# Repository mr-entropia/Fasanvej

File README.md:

# Fasanvej
A hand-held Linux computer, inspired by Brian Benchoff's similar project

## Features
- Allwinner F1C200s SoC, an ARM926EJ-S running at 500 MHz
- 64 MB DDR DRAM, embedded in the SoC
- 3.2" TFT LCD, 320x240 resolution
- QWERTY keyboard (implemented using a SAMD21 MCU, connects via USB)
- Game mode switch which alters key mapping
- USB hub with one external USB A connector
- Internal USB A type connector for a miniature WiFi adapter
- Mono speaker
- microSD slot
- SPI NOR FLASH
- Powered by 2P1S 18650 li-ion battery
- Built-in charger using a USB C type connector
- High efficiency DC-DC converters to power everything

## Task list
- [x] Finalize schematics
- [x] Place components on PCB
- [ ] Route PCB
- [x] Design a 3D-printable enclosure
- [ ] Source parts
- [ ] Build prototype
- [ ] Make software work
- [ ] Play DOOM

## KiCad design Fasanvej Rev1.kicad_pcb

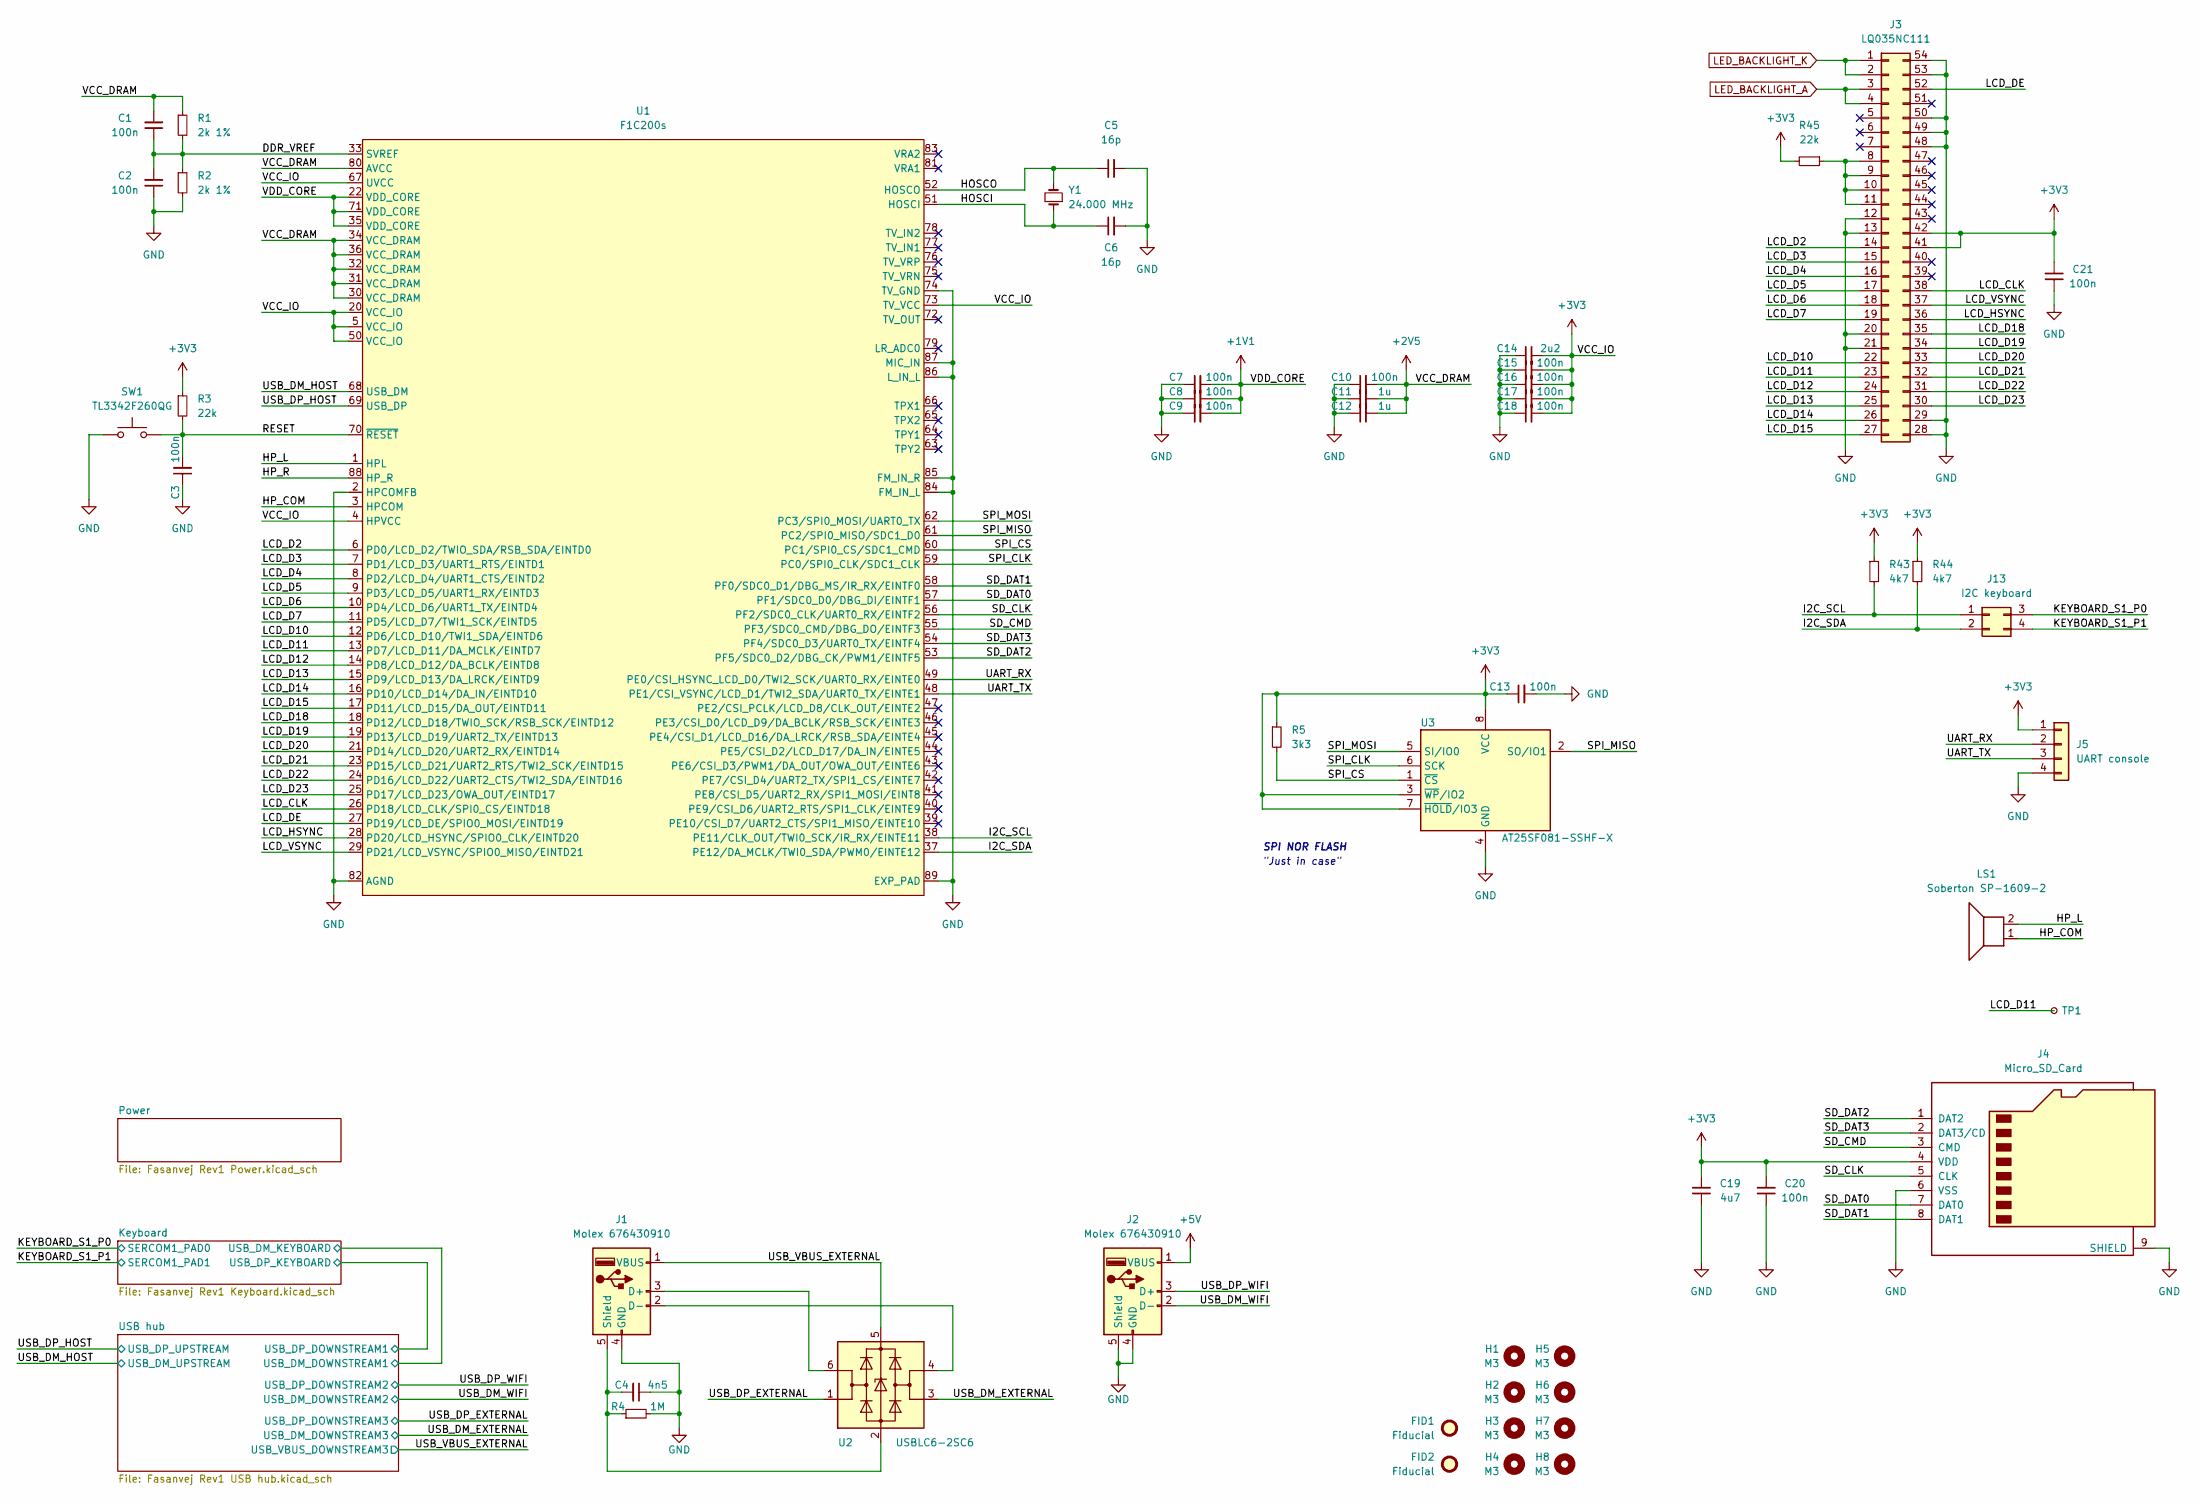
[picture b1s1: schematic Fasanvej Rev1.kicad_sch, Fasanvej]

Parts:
C1, C2, C3, C7, C8, C9, C10, C13, C15, C16, C17, C18, C20, C21: 100n; C_0603_1608Metric_Pad1.08x0.95mm_HandSolder
C4: 4n5; C_0603_1608Metric_Pad1.08x0.95mm_HandSolder
C5, C6: 16p; C_0603_1608Metric_Pad1.08x0.95mm_HandSolder
C11, C12: 1u; C_0805_2012Metric_Pad1.18x1.45mm_HandSolder
C14: 2u2; C_0805_2012Metric_Pad1.18x1.45mm_HandSolder
C19: 4u7; C_0805_2012Metric_Pad1.18x1.45mm_HandSolder
FID1, FID2: Fiducial; Fiducial_1.5mm_Mask3mm
H1, H2, H3, H4, H5, H6, H7, H8: M3; MountingHole_3.2mm_M3
J1, J2: Molex 676430910; USB_A_Molex_67643_Horizontal
J3: LQ035NC111; FFC2B22-54-T
J4: Micro_SD_Card; microSD_HC_Hirose_DM3D-SF
J5: UART console; PinHeader_1x04_P2.54mm_Vertical
J13: I2C keyboard; PinHeader_2x02_P2.54mm_Vertical
LS1: Soberton SP-1609-2; PinHeader_1x02_P2.54mm_Vertical
R1, R2: 2k 1%; R_0603_1608Metric_Pad0.98x0.95mm_HandSolder
R3, R45: 22k; R_0603_1608Metric_Pad0.98x0.95mm_HandSolder
R4: 1M; R_0603_1608Metric_Pad0.98x0.95mm_HandSolder
R5: 3k3; R_0603_1608Metric_Pad0.98x0.95mm_HandSolder
R43, R44: 4k7; R_0603_1608Metric_Pad0.98x0.95mm_HandSolder
SW1: TL3342F260QG; SW_SPST_TL3342
TP1: TestPoint_Small; TestPoint_Pad_D2.5mm
U1: F1C200s; QFN-88_EP_10x10_Pitch0.4mm
U2: USBLC6-2SC6; SOT-23-6
U3: AT25SF081-SSHF-X; SOIC-8_3.9x4.9mm_P1.27mm
Y1: 24.000 MHz; Crystal_SMD_HC49-SD_HandSoldering

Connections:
+1V1: C7.2, C8.2, C9.2, U1.22 (VDD_CORE), U1.35 (VDD_CORE), U1.71 (VDD_CORE); also elsewhere on the board
+2V5: C1.2, C10.2, C11.2, C12.2, R1.1, U1.30 (VCC_DRAM), U1.31 (VCC_DRAM), U1.32 (VCC_DRAM), U1.34 (VCC_DRAM), U1.36 (VCC_DRAM), U1.80 (AVCC); also elsewhere on the board
+3V3: C13.1, C14.2, C15.2, C16.2, C17.2, C18.2, C19.2, C20.2, C21.2, J3.41, J3.42, J4.4 (VDD), J5.1, R3.1, R5.1, R43.1, R44.1, R45.2, U1.4 (HPVCC), U1.5 (VCC_IO), U1.20 (VCC_IO), U1.50 (VCC_IO), U1.67 (UVCC), U1.73 (TV_VCC), U3.3 (~WP/IO2), U3.7 (~HOLD/IO3), U3.8 (VCC); also elsewhere on the board
+5V: J2.1 (VBUS); also elsewhere on the board
/DDR_VREF: C1.1, C2.2, R1.2, R2.1, U1.33 (SVREF)
/HOSCI: C6.1, U1.51 (HOSCI), Y1.1
/HOSCO: C5.1, U1.52 (HOSCO), Y1.2
/HP_COM: LS1.1, U1.3 (HPCOM)
/HP_L: LS1.2, U1.1 (HPL)
/HP_R: U1.88 (HP_R)
/I2C_SCL: J13.1, R43.2, U1.38 (PE11/CLK_OUT/TWI0_SCK/IR_RX/EINTE11)
/I2C_SDA: J13.2, R44.2, U1.37 (PE12/DA_MCLK/TWI0_SDA/PWM0/EINTE12)
/KEYBOARD_S1_P0: J13.3; also elsewhere on the board
/KEYBOARD_S1_P1: J13.4; also elsewhere on the board
/LCD_CLK: J3.38, U1.26 (PD18/LCD_CLK/SPI0_CS/EINTD18)
/LCD_D2: J3.14, U1.6 (PD0/LCD_D2/TWIO_SDA/RSB_SDA/EINTD0)
/LCD_D3: J3.15, U1.7 (PD1/LCD_D3/UART1_RTS/EINTD1)
/LCD_D4: J3.16, U1.8 (PD2/LCD_D4/UART1_CTS/EINTD2)
/LCD_D5: J3.17, U1.9 (PD3/LCD_D5/UART1_RX/EINTD3)
/LCD_D6: J3.18, U1.10 (PD4/LCD_D6/UART1_TX/EINTD4)
/LCD_D7: J3.19, U1.11 (PD5/LCD_D7/TWI1_SCK/EINTD5)
/LCD_D10: J3.22, U1.12 (PD6/LCD_D10/TWI1_SDA/EINTD6)
/LCD_D11: J3.23, TP1.1, U1.13 (PD7/LCD_D11/DA_MCLK/EINTD7)
/LCD_D12: J3.24, U1.14 (PD8/LCD_D12/DA_BCLK/EINTD8)
/LCD_D13: J3.25, U1.15 (PD9/LCD_D13/DA_LRCK/EINTD9)
/LCD_D14: J3.26, U1.16 (PD10/LCD_D14/DA_IN/EINTD10)
/LCD_D15: J3.27, U1.17 (PD11/LCD_D15/DA_OUT/EINTD11)
/LCD_D18: J3.35, U1.18 (PD12/LCD_D18/TWIO_SCK/RSB_SCK/EINTD12)
/LCD_D19: J3.34, U1.19 (PD13/LCD_D19/UART2_TX/EINTD13)
/LCD_D20: J3.33, U1.21 (PD14/LCD_D20/UART2_RX/EINTD14)
/LCD_D21: J3.32, U1.23 (PD15/LCD_D21/UART2_RTS/TWI2_SCK/EINTD15)
/LCD_D22: J3.31, U1.24 (PD16/LCD_D22/UART2_CTS/TWI2_SDA/EINTD16)
/LCD_D23: J3.30, U1.25 (PD17/LCD_D23/OWA_OUT/EINTD17)
/LCD_DE: J3.52, U1.27 (PD19/LCD_DE/SPIO0_MOSI/EINTD19)
/LCD_HSYNC: J3.36, U1.28 (PD20/LCD_HSYNC/SPIO0_CLK/EINTD20)
/LCD_VSYNC: J3.37, U1.29 (PD21/LCD_VSYNC/SPIO0_MISO/EINTD21)
/RESET: C3.2, R3.2, SW1.2, U1.70 (~RESET)
/SD_CLK: J4.5 (CLK), U1.56 (PF2/SDC0_CLK/UART0_RX/EINTF2)
/SD_CMD: J4.3 (CMD), U1.55 (PF3/SDC0_CMD/DBG_DO/EINTF3)
/SD_DAT0: J4.7 (DAT0), U1.57 (PF1/SDC0_D0/DBG_DI/EINTF1)
/SD_DAT1: J4.8 (DAT1), U1.58 (PF0/SDC0_D1/DBG_MS/IR_RX/EINTF0)
/SD_DAT2: J4.1 (DAT2), U1.53 (PF5/SDC0_D2/DBG_CK/PWM1/EINTF5)
/SD_DAT3: J4.2 (DAT3/CD), U1.54 (PF4/SDC0_D3/UART0_TX/EINTF4)
/SPI_CLK: U1.59 (PC0/SPI0_CLK/SDC1_CLK), U3.6 (SCK)
/SPI_CS: R5.2, U1.60 (PC1/SPI0_CS/SDC1_CMD), U3.1 (~CS)
/SPI_MISO: U1.61 (PC2/SPI0_MISO/SDC1_D0), U3.2 (SO/IO1)
/SPI_MOSI: U1.62 (PC3/SPI0_MOSI/UART0_TX), U3.5 (SI/IO0)
/UART_RX: J5.2, U1.49 (PE0/CSI_HSYNC_LCD_D0/TWI2_SCK/UART0_RX/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)
/UART_TX: J5.3, U1.48 (PE1/CSI_VSYNC/LCD_D1/TWI2_SDA/UART0_TX/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)
/USB_DM_EXTERNAL: U2.3 (I/O2); also elsewhere on the board
/USB_DM_HOST: U1.68 (USB_DM); also elsewhere on the board
/USB_DM_WIFI: J2.2 (D-); also elsewhere on the board
/USB_DP_EXTERNAL: U2.1 (I/O1); also elsewhere on the board
/USB_DP_HOST: U1.69 (USB_DP); also elsewhere on the board
/USB_DP_WIFI: J2.3 (D+); also elsewhere on the board
/USB_VBUS_EXTERNAL: J1.1 (VBUS), U2.5 (VBUS); also elsewhere on the board
GND: C2.1, C3.1, C4.1, C5.2, C6.2, C7.1, C8.1, C9.1, C10.1, C11.1, C12.1, C13.2, C14.1, C15.1, C16.1, C17.1, C18.1, C19.1, C20.1, C21.1, J1.4 (GND), J2.4 (GND), J2.5 (Shield), J3.12, J3.13, J3.20, J3.21, J3.28, J3.29, J3.48, J3.49, J3.50, J3.53, J3.54, J4.6 (VSS), J4.9 (SHIELD), J5.4, R2.2, R4.2, SW1.1, U1.2 (HPCOMFB), U1.74 (TV_GND), U1.82 (AGND), U1.84 (FM_IN_L), U1.85 (FM_IN_R), U1.86 (L_IN_L), U1.87 (MIC_IN), U1.89 (EXP_PAD), U3.4 (GND); also elsewhere on the board
LED_BACKLIGHT_A: J3.3, J3.4; also elsewhere on the board
LED_BACKLIGHT_K: J3.1, J3.2; also elsewhere on the board
unnamed: C4.2, J1.5 (Shield), R4.1, U2.2 (GND)
unnamed: J1.2 (D-), U2.4 (I/O2)
unnamed: J1.3 (D+), U2.6 (I/O1)
unnamed: J3.8, J3.9, J3.10, J3.11, R45.1

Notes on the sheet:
SPI NOR FLASH
"Just in case"

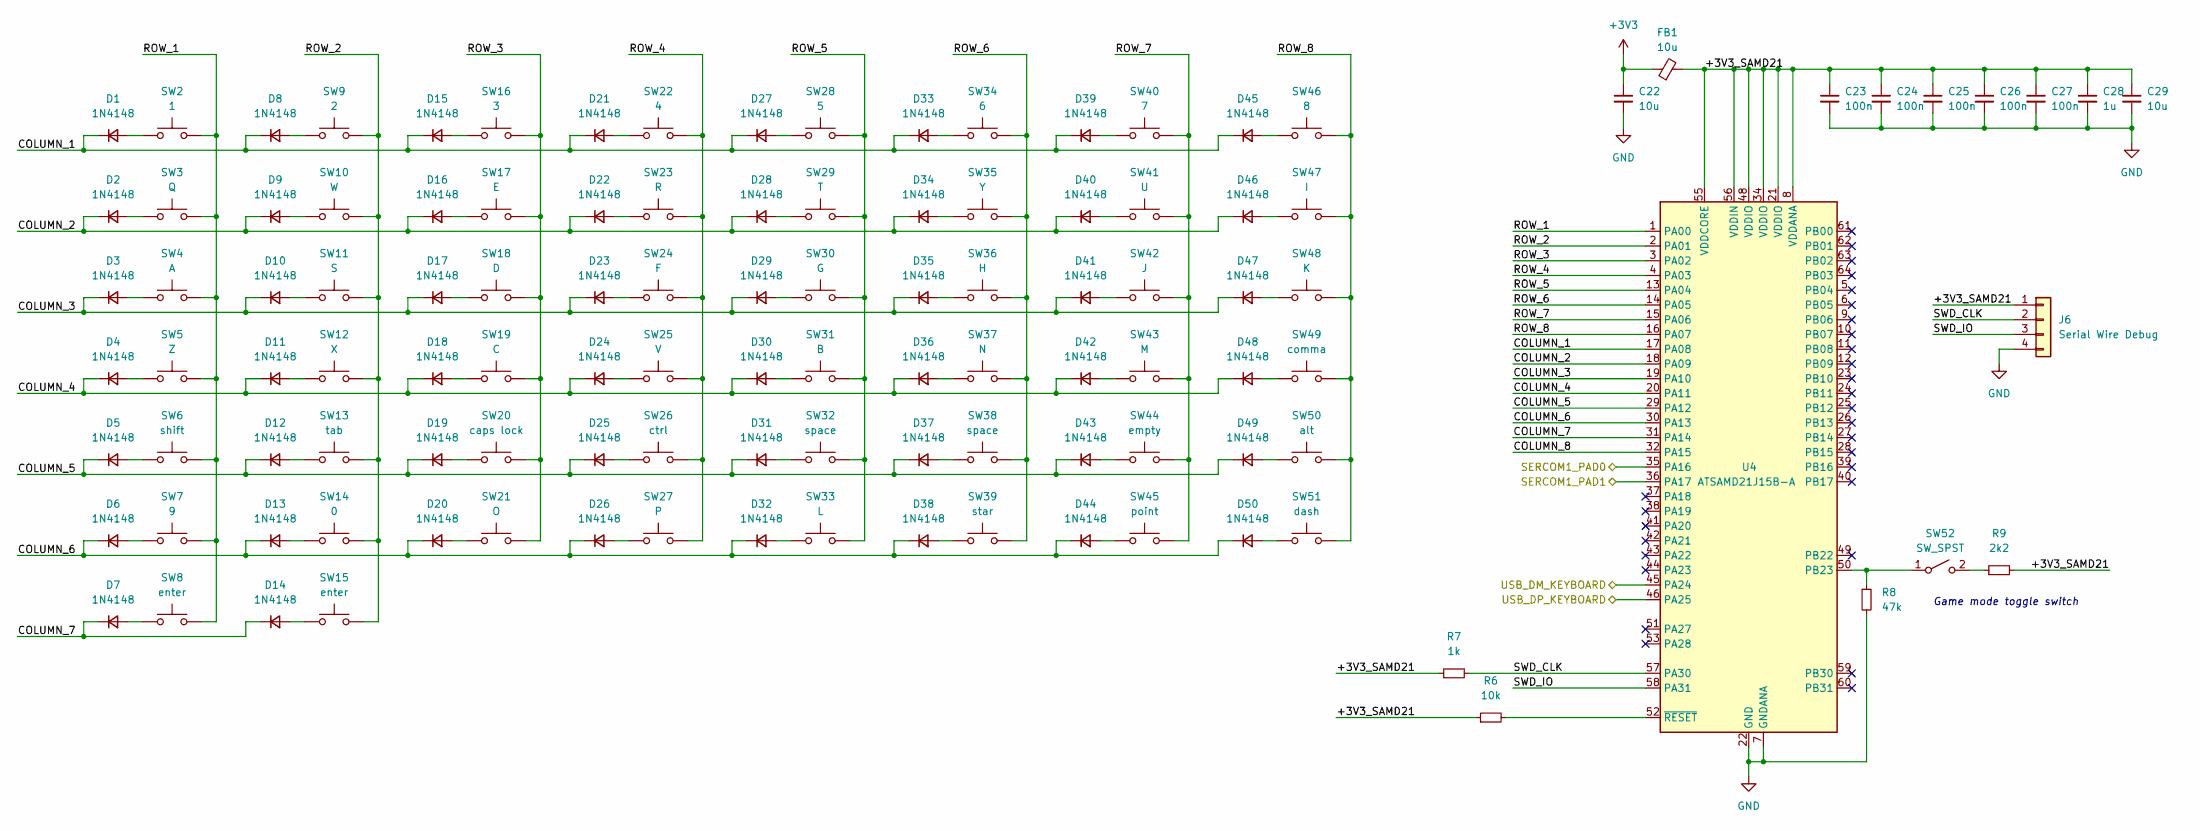
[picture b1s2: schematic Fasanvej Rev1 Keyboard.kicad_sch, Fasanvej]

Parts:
C22, C29: 10u; C_1206_3216Metric_Pad1.33x1.80mm_HandSolder
C23, C24, C25, C26, C27: 100n; C_0603_1608Metric_Pad1.08x0.95mm_HandSolder
C28: 1u; C_0603_1608Metric_Pad1.08x0.95mm_HandSolder
D1, D2, D3, D4, D5, D6, D7, D8, D9, D10, D11, D12, D13, D14, D15, D16, D17, D18, D19, D20, D21, D22, D23, D24, D25, D26, D27, D28, D29, D30, D31, D32, D33, D34, D35, D36, D37, D38, D39, D40, D41, D42, D43, D44, D45, D46, D47, D48, D49, D50: 1N4148; D_SOD-323_HandSoldering
FB1: 10u; L_1206_3216Metric_Pad1.22x1.90mm_HandSolder
J6: Serial Wire Debug; PinHeader_1x04_P2.54mm_Vertical
R6: 10k; R_0603_1608Metric_Pad0.98x0.95mm_HandSolder
R7: 1k; R_0603_1608Metric_Pad0.98x0.95mm_HandSolder
R8: 47k; R_0603_1608Metric_Pad0.98x0.95mm_HandSolder
R9: 2k2; R_0603_1608Metric_Pad0.98x0.95mm_HandSolder
SW2: 1; SW_SPST_TL3342
SW3: Q; SW_SPST_TL3342
SW4: A; SW_SPST_TL3342
SW5: Z; SW_SPST_TL3342
SW6: shift; SW_SPST_TL3342
SW7: 9; SW_SPST_TL3342
SW8, SW15: enter; SW_SPST_TL3342
SW9: 2; SW_SPST_TL3342
SW10: W; SW_SPST_TL3342
SW11: S; SW_SPST_TL3342
SW12: X; SW_SPST_TL3342
SW13: tab; SW_SPST_TL3342
SW14: 0; SW_SPST_TL3342
SW16: 3; SW_SPST_TL3342
SW17: E; SW_SPST_TL3342
SW18: D; SW_SPST_TL3342
SW19: C; SW_SPST_TL3342
SW20: caps lock; SW_SPST_TL3342
SW21: O; SW_SPST_TL3342
SW22: 4; SW_SPST_TL3342
SW23: R; SW_SPST_TL3342
SW24: F; SW_SPST_TL3342
SW25: V; SW_SPST_TL3342
SW26: ctrl; SW_SPST_TL3342
SW27: P; SW_SPST_TL3342
SW28: 5; SW_SPST_TL3342
SW29: T; SW_SPST_TL3342
SW30: G; SW_SPST_TL3342
SW31: B; SW_SPST_TL3342
SW32, SW38: space; SW_SPST_TL3342
SW33: L; SW_SPST_TL3342
SW34: 6; SW_SPST_TL3342
SW35: Y; SW_SPST_TL3342
SW36: H; SW_SPST_TL3342
SW37: N; SW_SPST_TL3342
SW39: star; SW_SPST_TL3342
SW40: 7; SW_SPST_TL3342
SW41: U; SW_SPST_TL3342
SW42: J; SW_SPST_TL3342
SW43: M; SW_SPST_TL3342
SW44: empty; SW_SPST_TL3342
SW45: point; SW_SPST_TL3342
SW46: 8; SW_SPST_TL3342
SW47: I; SW_SPST_TL3342
SW48: K; SW_SPST_TL3342
SW49: comma; SW_SPST_TL3342
SW50: alt; SW_SPST_TL3342
SW51: dash; SW_SPST_TL3342
SW52: SW_SPST; SW_CuK_JS202011AQN_DPDT_Angled
U4: ATSAMD21J15B-A; TQFP-64_10x10mm_P0.5mm

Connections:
+3V3: C22.1, FB1.1; also elsewhere on the board
/KEYBOARD_S1_P0: U4.35 (PA16); also elsewhere on the board
/KEYBOARD_S1_P1: U4.36 (PA17); also elsewhere on the board
/Keyboard/+3V3_SAMD21: C23.1, C24.1, C25.1, C26.1, C27.1, C28.1, C29.1, FB1.2, J6.1, R6.1, R7.1, R9.2, U4.8 (VDDANA), U4.21 (VDDIO), U4.34 (VDDIO), U4.48 (VDDIO), U4.55 (VDDCORE), U4.56 (VDDIN)
/Keyboard/COLUMN_1: D1.1 (K), D8.1 (K), D15.1 (K), D21.1 (K), D27.1 (K), D33.1 (K), D39.1 (K), D45.1 (K), U4.17 (PA08)
/Keyboard/COLUMN_2: D2.1 (K), D9.1 (K), D16.1 (K), D22.1 (K), D28.1 (K), D34.1 (K), D40.1 (K), D46.1 (K), U4.18 (PA09)
/Keyboard/COLUMN_3: D3.1 (K), D10.1 (K), D17.1 (K), D23.1 (K), D29.1 (K), D35.1 (K), D41.1 (K), D47.1 (K), U4.19 (PA10)
/Keyboard/COLUMN_4: D4.1 (K), D11.1 (K), D18.1 (K), D24.1 (K), D30.1 (K), D36.1 (K), D42.1 (K), D48.1 (K), U4.20 (PA11)
/Keyboard/COLUMN_5: D5.1 (K), D12.1 (K), D19.1 (K), D25.1 (K), D31.1 (K), D37.1 (K), D43.1 (K), D49.1 (K), U4.29 (PA12)
/Keyboard/COLUMN_6: D6.1 (K), D13.1 (K), D20.1 (K), D26.1 (K), D32.1 (K), D38.1 (K), D44.1 (K), D50.1 (K), U4.30 (PA13)
/Keyboard/COLUMN_7: D7.1 (K), D14.1 (K), U4.31 (PA14)
/Keyboard/COLUMN_8: U4.32 (PA15)
/Keyboard/ROW_1: SW2.2, SW3.2, SW4.2, SW5.2, SW6.2, SW7.2, SW8.2, U4.1 (PA00)
/Keyboard/ROW_2: SW9.2, SW10.2, SW11.2, SW12.2, SW13.2, SW14.2, SW15.2, U4.2 (PA01)
/Keyboard/ROW_3: SW16.2, SW17.2, SW18.2, SW19.2, SW20.2, SW21.2, U4.3 (PA02)
/Keyboard/ROW_4: SW22.2, SW23.2, SW24.2, SW25.2, SW26.2, SW27.2, U4.4 (PA03)
/Keyboard/ROW_5: SW28.2, SW29.2, SW30.2, SW31.2, SW32.2, SW33.2, U4.13 (PA04)
/Keyboard/ROW_6: SW34.2, SW35.2, SW36.2, SW37.2, SW38.2, SW39.2, U4.14 (PA05)
/Keyboard/ROW_7: SW40.2, SW41.2, SW42.2, SW43.2, SW44.2, SW45.2, U4.15 (PA06)
/Keyboard/ROW_8: SW46.2, SW47.2, SW48.2, SW49.2, SW50.2, SW51.2, U4.16 (PA07)
/Keyboard/SWD_CLK: J6.2, R7.2, U4.57 (PA30)
/Keyboard/SWD_IO: J6.3, U4.58 (PA31)
/Keyboard/USB_DM_KEYBOARD: U4.45 (PA24); also elsewhere on the board
/Keyboard/USB_DP_KEYBOARD: U4.46 (PA25); also elsewhere on the board
GND: C22.2, C23.2, C24.2, C25.2, C26.2, C27.2, C28.2, C29.2, J6.4, R8.2, U4.7 (GNDANA), U4.22 (GND), U4.33 (GND), U4.47 (GND), U4.54 (GND); also elsewhere on the board
unnamed: D1.2 (A), SW2.1
unnamed: D2.2 (A), SW3.1
unnamed: D3.2 (A), SW4.1
unnamed: D4.2 (A), SW5.1
unnamed: D5.2 (A), SW6.1
unnamed: D6.2 (A), SW7.1
unnamed: D7.2 (A), SW8.1
unnamed: D8.2 (A), SW9.1
unnamed: D9.2 (A), SW10.1
unnamed: D10.2 (A), SW11.1
unnamed: D11.2 (A), SW12.1
unnamed: D12.2 (A), SW13.1
unnamed: D13.2 (A), SW14.1
unnamed: D14.2 (A), SW15.1
unnamed: D15.2 (A), SW16.1
unnamed: D16.2 (A), SW17.1
unnamed: D17.2 (A), SW18.1
unnamed: D18.2 (A), SW19.1
unnamed: D19.2 (A), SW20.1
unnamed: D20.2 (A), SW21.1
unnamed: D21.2 (A), SW22.1
unnamed: D22.2 (A), SW23.1
unnamed: D23.2 (A), SW24.1
unnamed: D24.2 (A), SW25.1
unnamed: D25.2 (A), SW26.1
unnamed: D26.2 (A), SW27.1
unnamed: D27.2 (A), SW28.1
unnamed: D28.2 (A), SW29.1
unnamed: D29.2 (A), SW30.1
unnamed: D30.2 (A), SW31.1
unnamed: D31.2 (A), SW32.1
unnamed: D32.2 (A), SW33.1
unnamed: D33.2 (A), SW34.1
unnamed: D34.2 (A), SW35.1
unnamed: D35.2 (A), SW36.1
unnamed: D36.2 (A), SW37.1
unnamed: D37.2 (A), SW38.1
unnamed: D38.2 (A), SW39.1
unnamed: D39.2 (A), SW40.1
unnamed: D40.2 (A), SW41.1
unnamed: D41.2 (A), SW42.1
unnamed: D42.2 (A), SW43.1
unnamed: D43.2 (A), SW44.1
unnamed: D44.2 (A), SW45.1
unnamed: D45.2 (A), SW46.1
unnamed: D46.2 (A), SW47.1
unnamed: D47.2 (A), SW48.1
unnamed: D48.2 (A), SW49.1
unnamed: D49.2 (A), SW50.1
unnamed: D50.2 (A), SW51.1
unnamed: R6.2, U4.52 (~RESET)
unnamed: R8.1, SW52.1 (A), U4.50 (PB23)
unnamed: R9.1, SW52.2 (B)

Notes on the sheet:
Game mode toggle switch

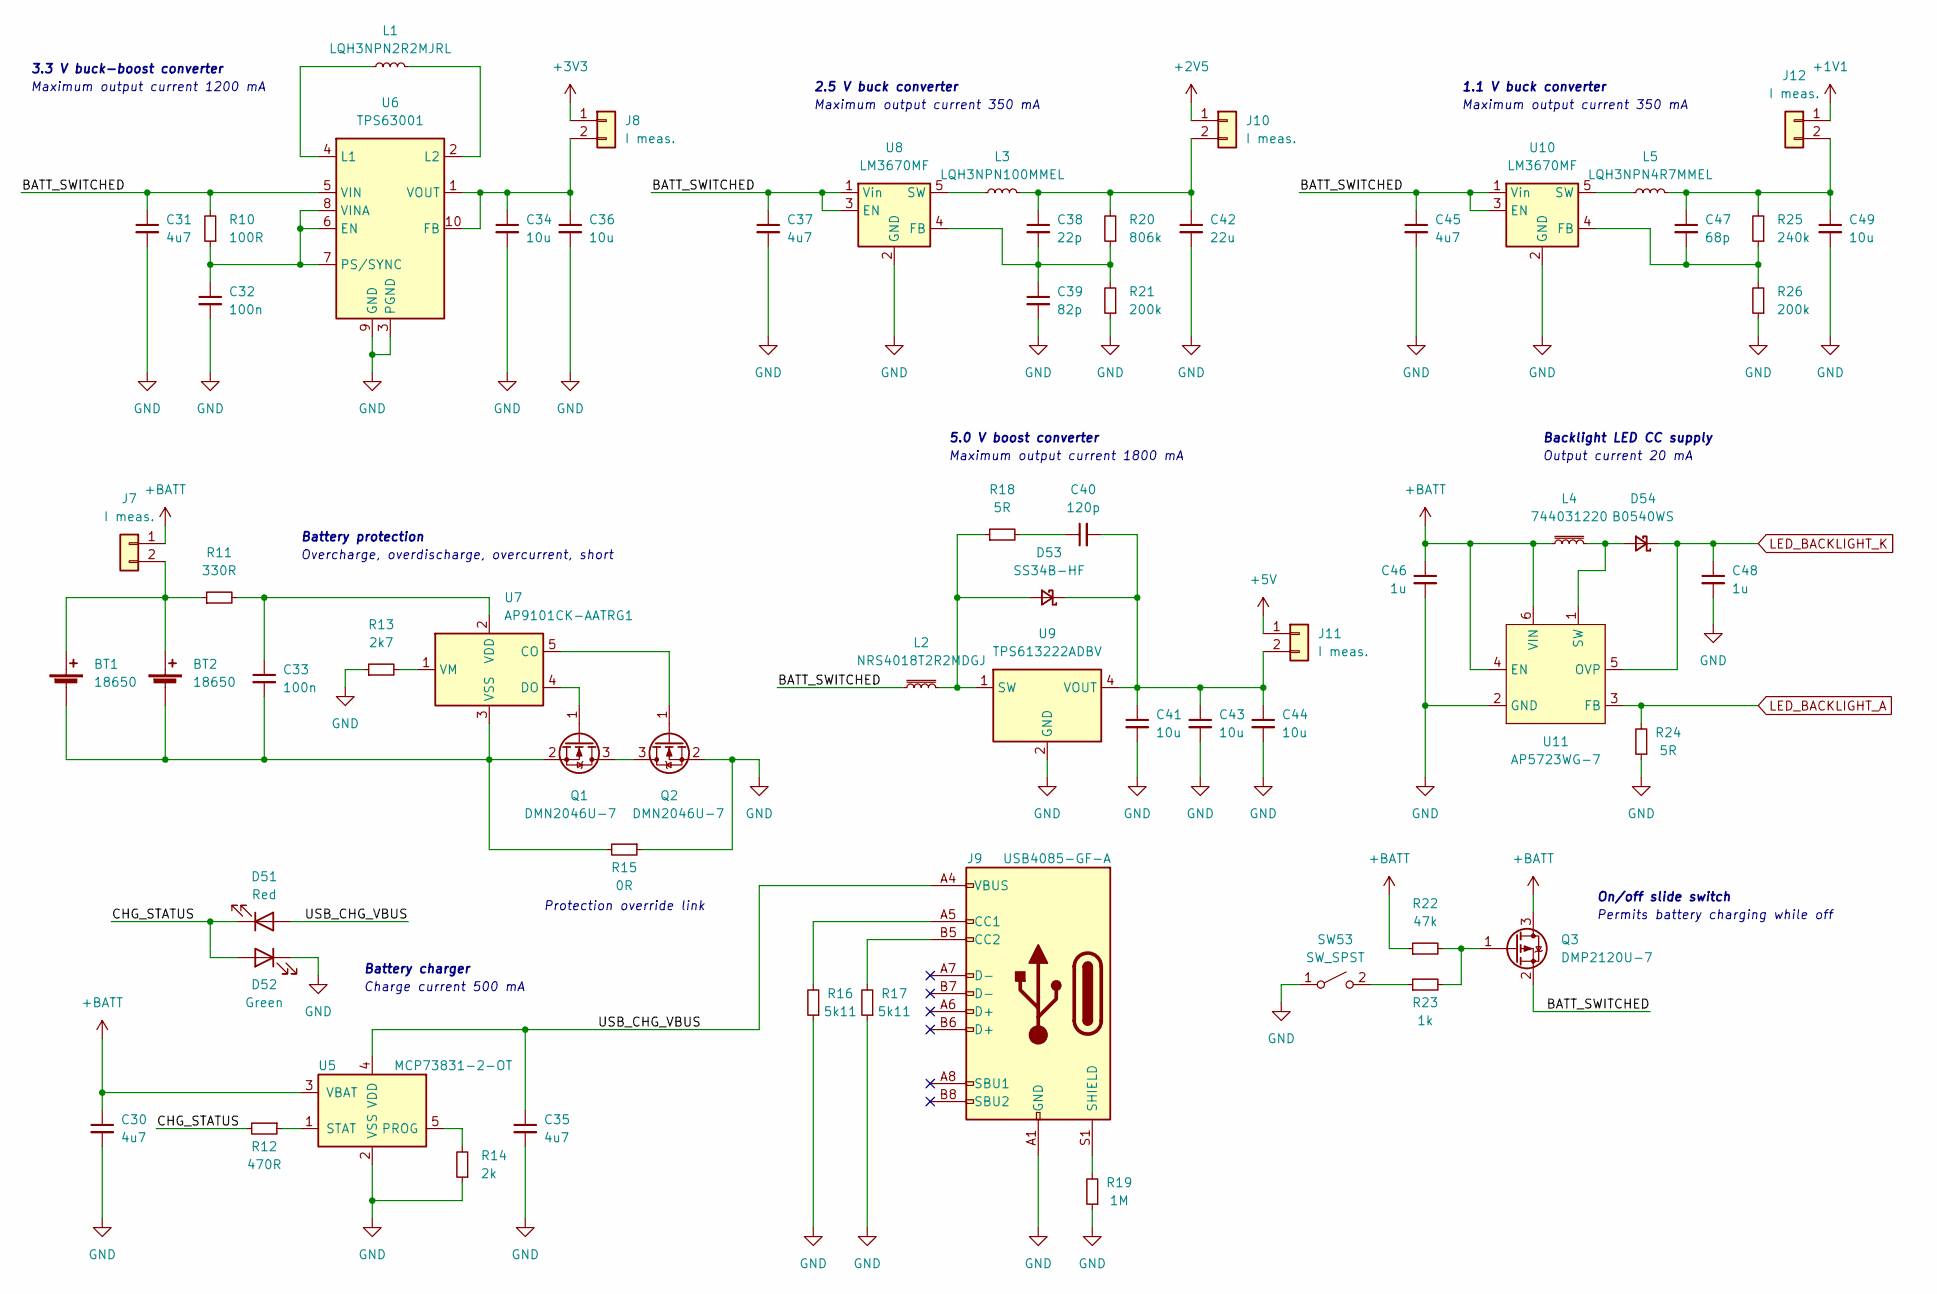
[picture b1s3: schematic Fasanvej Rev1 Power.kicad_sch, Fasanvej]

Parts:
BT1, BT2: 18650; BatteryHolder_Keystone_1042_1x18650
C30, C31, C35, C37, C45: 4u7; C_1206_3216Metric_Pad1.33x1.80mm_HandSolder
C32, C33: 100n; C_0603_1608Metric_Pad1.08x0.95mm_HandSolder
C34, C36, C41, C43, C44: 10u; C_1210_3225Metric_Pad1.33x2.70mm_HandSolder
C38: 22p; C_0603_1608Metric_Pad1.08x0.95mm_HandSolder
C39: 82p; C_0603_1608Metric_Pad1.08x0.95mm_HandSolder
C40: 120p; C_0603_1608Metric_Pad1.08x0.95mm_HandSolder
C42: 22u; C_1210_3225Metric_Pad1.33x2.70mm_HandSolder
C46, C48: 1u; C_0805_2012Metric_Pad1.18x1.45mm_HandSolder
C47: 68p; C_0603_1608Metric_Pad1.08x0.95mm_HandSolder
C49: 10u; C_1206_3216Metric_Pad1.33x1.80mm_HandSolder
D51: Red; LED_0805_2012Metric_Pad1.15x1.40mm_HandSolder
D52: Green; LED_0805_2012Metric_Pad1.15x1.40mm_HandSolder
D53: SS34B-HF; D_SMB_Handsoldering
D54: B0540WS; D_SOD-323_HandSoldering
J7, J8, J10, J11, J12: I meas.; PinHeader_1x02_P2.54mm_Vertical
J9: USB4085-GF-A; USB_C_Receptacle_GCT_USB4085
L1: LQH3NPN2R2MJRL; L_SMD_3030
L2: NRS4018T2R2MDGJ; L_Taiyo-Yuden_NR-40xx_HandSoldering
L3: LQH3NPN100MMEL; L_SMD_3030
L4: 744031220; L_Wuerth_WE-TPC-3816
L5: LQH3NPN4R7MMEL; L_SMD_3030
Q1, Q2: DMN2046U-7; SOT-23_Handsoldering
Q3: DMP2120U-7; SOT-23_Handsoldering
R10: 100R; R_0603_1608Metric_Pad0.98x0.95mm_HandSolder
R11: 330R; R_1206_3216Metric_Pad1.30x1.75mm_HandSolder
R12: 470R; R_0603_1608Metric_Pad0.98x0.95mm_HandSolder
R13: 2k7; R_1206_3216Metric_Pad1.30x1.75mm_HandSolder
R14: 2k; R_0603_1608Metric_Pad0.98x0.95mm_HandSolder
R15: 0R; R_1210_3225Metric_Pad1.30x2.65mm_HandSolder
R16, R17: 5k11; R_0603_1608Metric_Pad0.98x0.95mm_HandSolder
R18: 5R; R_0603_1608Metric_Pad0.98x0.95mm_HandSolder
R19: 1M; R_0603_1608Metric_Pad0.98x0.95mm_HandSolder
R20: 806k; R_0603_1608Metric_Pad0.98x0.95mm_HandSolder
R21, R26: 200k; R_0603_1608Metric_Pad0.98x0.95mm_HandSolder
R22: 47k; R_0603_1608Metric_Pad0.98x0.95mm_HandSolder
R23: 1k; R_0603_1608Metric_Pad0.98x0.95mm_HandSolder
R24: 5R; R_1210_3225Metric_Pad1.30x2.65mm_HandSolder
R25: 240k; R_0603_1608Metric_Pad0.98x0.95mm_HandSolder
SW53: SW_SPST; SW_CuK_JS202011AQN_DPDT_Angled
U5: MCP73831-2-OT; SOT-23-5
U6: TPS63001; Texas_DRC0010J_ThermalVias
U7: AP9101CK-AATRG1; SOT-23-5
U8, U10: LM3670MF; TSOT-23-5
U9: TPS613222ADBV; SOT-23-5
U11: AP5723WG-7; SOT-23-6_Handsoldering

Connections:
+1V1: J12.1; also elsewhere on the board
+2V5: J10.1; also elsewhere on the board
+3V3: J8.1; also elsewhere on the board
+5V: J11.1; also elsewhere on the board
+BATT: C30.1, C46.1, J7.1, L4.1, Q3.3 (D), R22.1, U5.3 (VBAT), U11.4 (EN), U11.6 (VIN)
/Power/BATT_SWITCHED: C31.1, C37.1, C45.1, L2.1, Q3.2 (S), R10.2, U6.5 (VIN), U8.1 (Vin), U8.3 (EN), U10.1 (Vin), U10.3 (EN)
/Power/CHG_STATUS: D51.1 (K), D52.2 (A), R12.2
/Power/USB_CHG_VBUS: C35.1, D51.2 (A), J9.A4 (VBUS), J9.A9 (VBUS), J9.B4 (VBUS), J9.B9 (VBUS), U5.4 (VDD)
GND: C30.2, C31.2, C32.2, C34.2, C35.2, C36.2, C37.2, C39.2, C41.2, C42.2, C43.2, C44.2, C45.2, C46.2, C48.2, C49.2, D52.1 (K), J9.A1 (GND), J9.A12 (GND), J9.B1 (GND), J9.B12 (GND), Q2.2 (S), R13.1, R14.1, R15.1, R16.1, R17.1, R19.1, R21.1, R24.1, R26.1, SW53.1 (A), U5.2 (VSS), U6.3 (PGND), U6.9 (GND), U6.11 (PGND), U8.2 (GND), U9.2 (GND), U10.2 (GND), U11.2 (GND); also elsewhere on the board
LED_BACKLIGHT_A: R24.2, U11.3 (FB); also elsewhere on the board
LED_BACKLIGHT_K: C48.1, D54.1 (K), U11.5 (OVP); also elsewhere on the board
unnamed: BT1.1 (+), BT2.1 (+), J7.2, R11.1
unnamed: BT1.2 (-), BT2.2 (-), C33.2, Q1.2 (S), R15.2, U7.3 (VSS)
unnamed: C32.1, R10.1, U6.6 (EN), U6.7 (PS/SYNC), U6.8 (VINA)
unnamed: C33.1, R11.2, U7.2 (VDD)
unnamed: C34.1, C36.1, J8.2, U6.1 (VOUT), U6.10 (FB)
unnamed: C38.1, C42.1, J10.2, L3.2, R20.2
unnamed: C38.2, C39.1, R20.1, R21.2, U8.4 (FB)
unnamed: C40.1, R18.2
unnamed: C40.2, C41.1, C43.1, C44.1, D53.1 (K), J11.2, U9.4 (VOUT)
unnamed: C47.1, C49.1, J12.2, L5.2, R25.2
unnamed: C47.2, R25.1, R26.2, U10.4 (FB)
unnamed: D53.2 (A), L2.2, R18.1, U9.1 (SW)
unnamed: D54.2 (A), L4.2, U11.1 (SW)
unnamed: J9.A5 (CC1), R16.2
unnamed: J9.B5 (CC2), R17.2
unnamed: J9.S1 (SHIELD), R19.2
unnamed: L1.1, U6.4 (L1)
unnamed: L1.2, U6.2 (L2)
unnamed: L3.1, U8.5 (SW)
unnamed: L5.1, U10.5 (SW)
unnamed: Q1.1 (G), U7.4 (DO)
unnamed: Q1.3 (D), Q2.3 (D)
unnamed: Q2.1 (G), U7.5 (CO)
unnamed: Q3.1 (G), R22.2, R23.2
unnamed: R12.1, U5.1 (STAT)
unnamed: R13.2, U7.1 (VM)
unnamed: R14.2, U5.5 (PROG)
unnamed: R23.1, SW53.2 (B)

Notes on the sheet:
Maximum output current 350 mA
Output current 20 mA
Permits battery charging while off
Charge current 500 mA
Protection override link
Battery charger
3.3 V buck-boost converter
Overcharge, overdischarge, overcurrent, short
Backlight LED CC supply
1.1 V buck converter
5.0 V boost converter
Maximum output current 1200 mA
2.5 V buck converter
Maximum output current 1800 mA
On/off slide switch
Battery protection

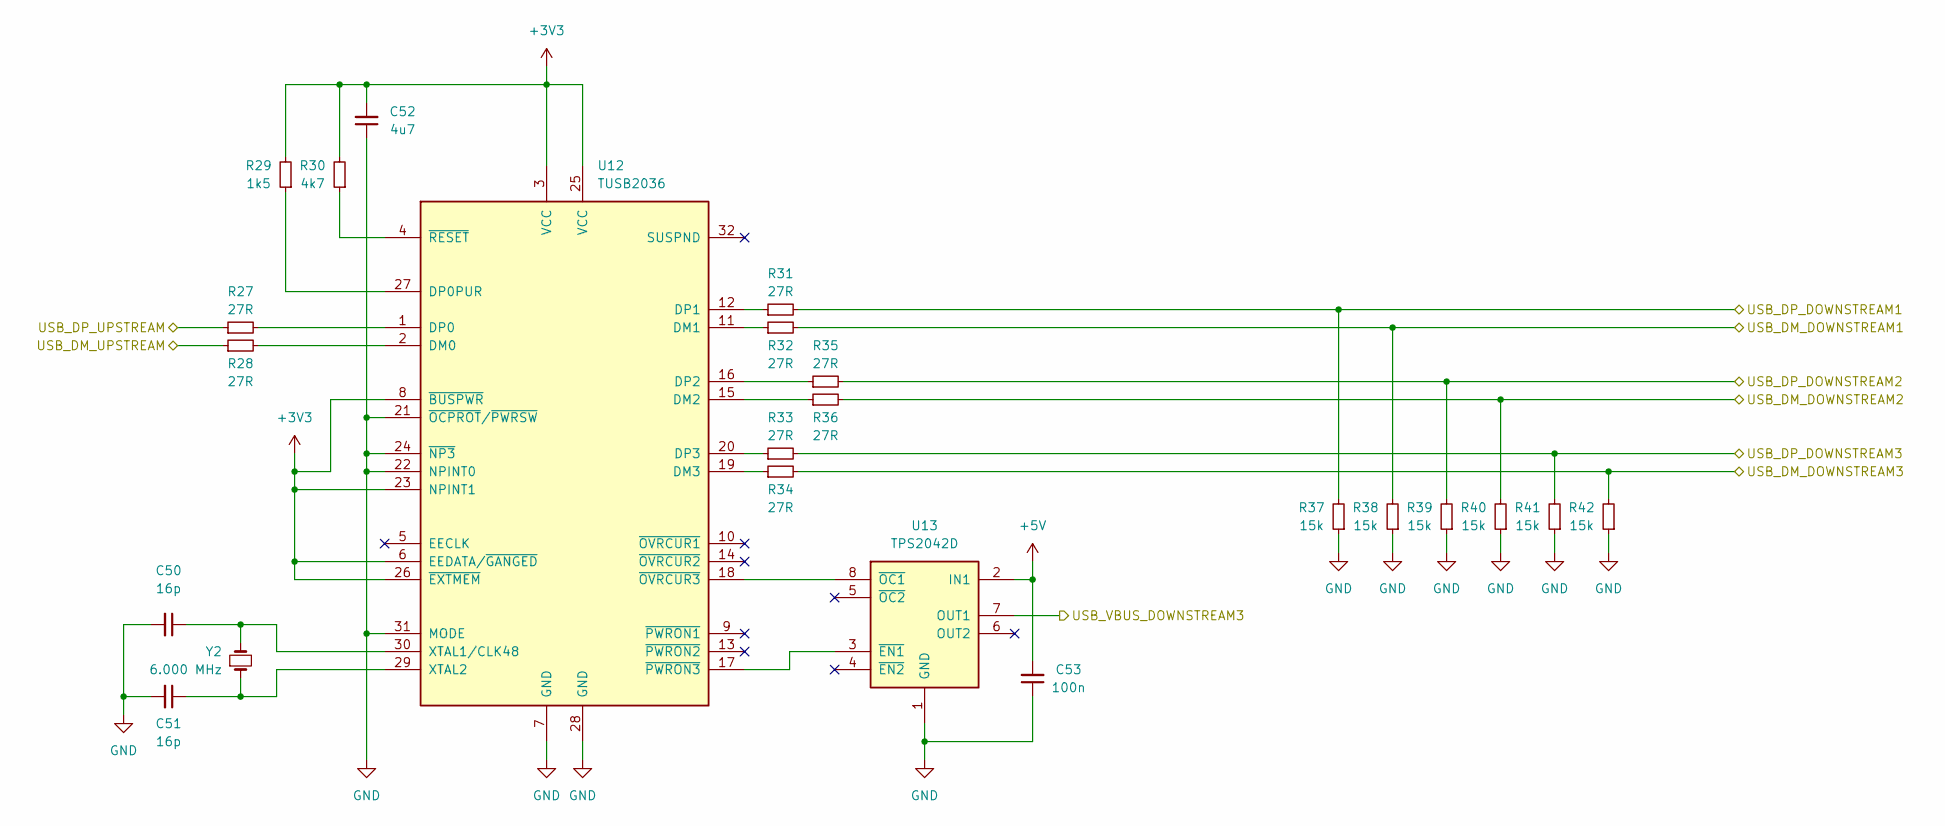
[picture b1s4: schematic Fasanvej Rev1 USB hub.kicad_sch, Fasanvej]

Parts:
C50, C51: 16p; C_0603_1608Metric_Pad1.08x0.95mm_HandSolder
C52: 4u7; C_1206_3216Metric_Pad1.33x1.80mm_HandSolder
C53: 100n; C_0603_1608Metric_Pad1.08x0.95mm_HandSolder
R27, R28, R31, R32, R33, R34, R35, R36: 27R; R_0603_1608Metric_Pad0.98x0.95mm_HandSolder
R29: 1k5; R_0603_1608Metric_Pad0.98x0.95mm_HandSolder
R30: 4k7; R_0603_1608Metric_Pad0.98x0.95mm_HandSolder
R37, R38, R39, R40, R41, R42: 15k; R_0603_1608Metric_Pad0.98x0.95mm_HandSolder
U12: TUSB2036; LQFP-32_7x7mm_P0.8mm
U13: TPS2042D; SOIC-8_3.9x4.9mm_P1.27mm
Y2: 6.000 MHz; Crystal_SMD_HC49-SD_HandSoldering

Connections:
+3V3: C52.2, R29.2, R30.2, U12.3 (VCC), U12.6 (EEDATA/~GANGED), U12.8 (~BUSPWR), U12.23 (NPINT1), U12.25 (VCC), U12.26 (~EXTMEM); also elsewhere on the board
+5V: C53.2, U13.2 (IN1); also elsewhere on the board
/Keyboard/USB_DM_KEYBOARD: R32.2, R38.2; also elsewhere on the board
/Keyboard/USB_DP_KEYBOARD: R31.2, R37.2; also elsewhere on the board
/USB_DM_EXTERNAL: R34.2, R42.2; also elsewhere on the board
/USB_DM_HOST: R28.1; also elsewhere on the board
/USB_DM_WIFI: R36.2, R40.2; also elsewhere on the board
/USB_DP_EXTERNAL: R33.2, R41.2; also elsewhere on the board
/USB_DP_HOST: R27.1; also elsewhere on the board
/USB_DP_WIFI: R35.2, R39.2; also elsewhere on the board
/USB_VBUS_EXTERNAL: U13.7 (OUT1); also elsewhere on the board
GND: C50.2, C51.2, C52.1, C53.1, R37.1, R38.1, R39.1, R40.1, R41.1, R42.1, U12.7 (GND), U12.21 (~OCPROT/~PWRSW), U12.22 (NPINT0), U12.24 (~NP3), U12.28 (GND), U12.31 (MODE), U13.1 (GND); also elsewhere on the board
unnamed: C50.1, U12.30 (XTAL1/CLK48), Y2.2
unnamed: C51.1, U12.29 (XTAL2), Y2.1
unnamed: R27.2, U12.1 (DP0)
unnamed: R28.2, U12.2 (DM0)
unnamed: R29.1, U12.27 (DP0PUR)
unnamed: R30.1, U12.4 (~RESET)
unnamed: R31.1, U12.12 (DP1)
unnamed: R32.1, U12.11 (DM1)
unnamed: R33.1, U12.20 (DP3)
unnamed: R34.1, U12.19 (DM3)
unnamed: R35.1, U12.16 (DP2)
unnamed: R36.1, U12.15 (DM2)
unnamed: U12.17 (~PWRON3), U13.3 (~EN1)
unnamed: U12.18 (~OVRCUR3), U13.8 (~OC1)

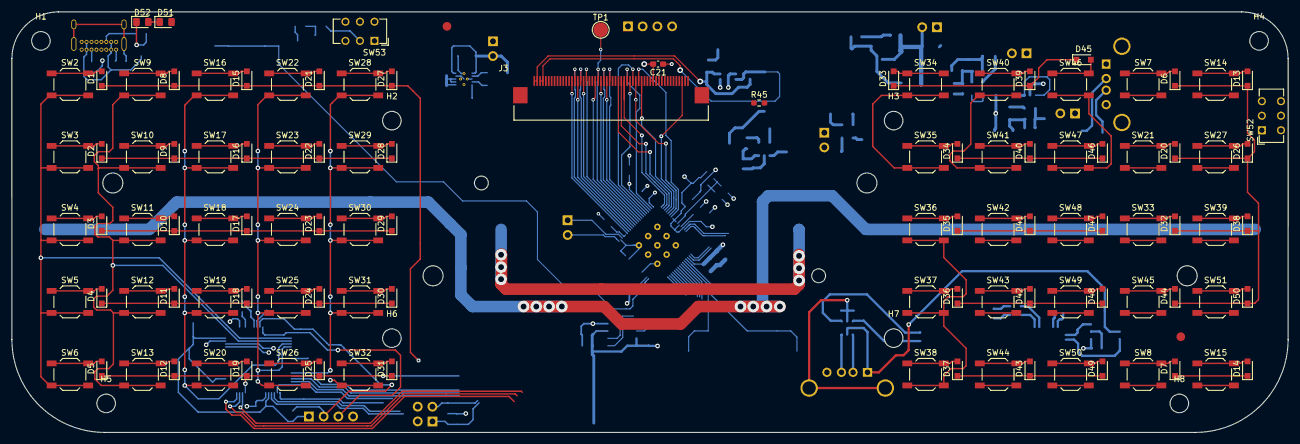
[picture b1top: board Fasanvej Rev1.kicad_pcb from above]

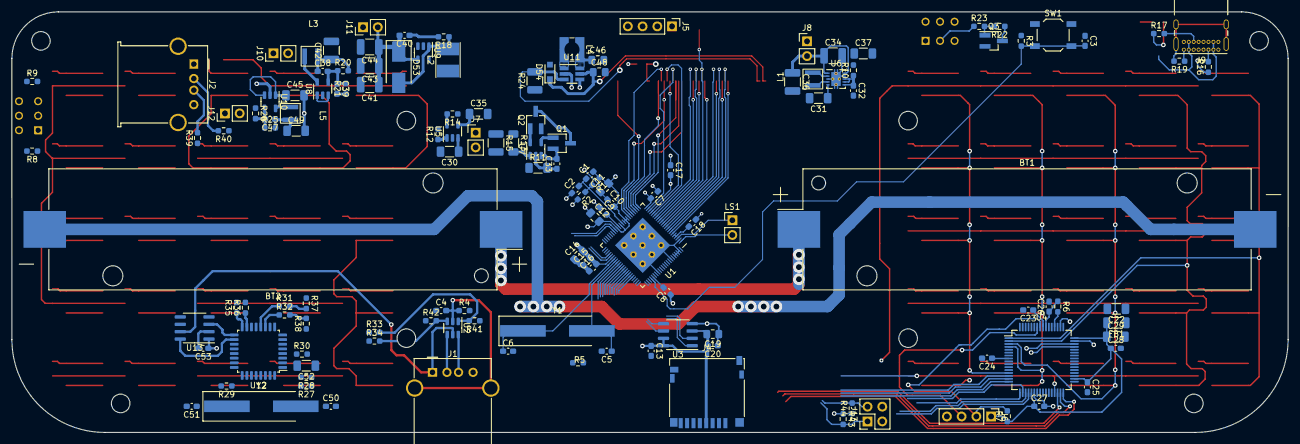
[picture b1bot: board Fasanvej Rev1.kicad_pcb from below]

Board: 2 copper layers, 220.0 x 72.5 mm, 256 parts (138 on the bottom side), 181 nets.

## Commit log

2022-02-17 Added SPI NOR FLASH. Finished power connections to SoC. Added SWD for keyboard MCU. Improved USB ESD protection. Finished all SoC connections. Added DDR VREF divider.
2022-02-21 Finished schematics. Pending validation.
2022-02-22 Finalized schematics some more. Still missing a few footprints.
2022-02-24 Schematic finalized. Started PCB layout.
2022-02-24 Started placing components
2022-02-27 Added keymap
2022-02-27 Made a lot of progress laying out PCB
2022-03-02 Made progress with board layout as well as mechanical (case) design
2022-03-04 Made progress with PCB layout. Preliminary case design added.
